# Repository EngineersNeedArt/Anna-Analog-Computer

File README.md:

# “Anna” Analog Computer

***Anna*** is an ecosystem of analog computing modules. The modules (each about the size of a matchbook) make use of a hobbyist breadboard and USB power that combine to make something like an analog computer trainer.

### Breadboard

An electronics breadboard is an integral part of ***Anna***. The breadboard allows ***Anna*** to be easily modular, expandable. It provides a power bus (the top two power rails of the breadboard) and it is acts as the “patch bay” that allows you to connect inputs and outputs between the various analog operators.

### Power

The modules comprising ***Anna*** all run on (nominally 5V) USB power. All modules but **MAIN** assume that the top two power rails of the breadboard supply this USB power. The top rail (row) of the breadboard is assumed to be +5V and the rail (row) below is assumed to be ground (GND).

While these power rails operate the electronics for each module, these rails are not to be used for the analog *programming*. There are instead three reference voltages used in the analog computing domain. These are:
- **+UNIT**, nominally 4.00V. Representing the largest machine value (+1 if you like).
- **ZERO**, nominally 2.50V. Representing the machine value zero (0).
- **-UNIT**, nominally 1.00V. Representing the smallest machine value (-1 if you like).
Needless to say, this makes the voltage window for representing values in ***Anna*** a very narrow 3 volts. Perhaps this is a good time to remind you that it is intended to be a *hobbyist* analog computer. 

## **The Modules**

### MAIN Module

The **MAIN** module is required for any ***Anna*** configuration as it provides USB power to the top two rails of the breadboard. These USB power rails are what all other ***Anna*** modules depend upon to operate.
- Provides USB power to the top two power rails on the breadboard—powering all other ***Anna*** modules.
- Provides the reference voltages for **+UNIT**, **ZERO** and **-UNIT**. These are the operating voltages of the analog computer programs.
- Inputs for up to five source voltages for display on the color LCD.
- Numerous metering modes (can be cycled through using the top button on the module).
- Overload LED (and output pin) indicate when a source voltage is out of range (higher than **+UNIT** or lower than **-UNIT**).

More (esoteric) details are available in the **README** that with the **MAIN** subfolder in this repository.

### POTS Module

The **POTS** module, as with the remaining modules described, is to be inserted into a breadboard such that its power pins engage in the top two power rails (top-most row: **USB 5V**, the row just below: **GND**). As described above, the **USB** power is provided by the **MAIN** board.

The **POTS** has four potentiometers—three of those are wired internally to behave as “coefficient multipliers” (in analog computer parlance). What this means, electrically, is that the low-side of the potentiometer is tied to a *machine zero* reference supplies by **MAIN**, while the user is expected to connect their input signal to the pin tied to the potʼs high-side. With the potʼs wiper connected to the output pin, the pot acts as a voltage divider—effectively attenuating the incoming voltage.

A practical use case for a coefficient multiplier is to attenuate a signal that is being used as feedback.

The 4th potentiometer on the **POTS** module is not tied to a zero-reference—the high-side of the pot is another input pin. The input pins are labeled **CCW** and **CW** referring to the rotation of the pot they correspond to. Connecting **CCW** to a **ZERO** reference makes this 4th pot behave like the other three—like a coefficient multiplier.

Like all of the modules (except for **MAIN**), **POTS** requires a **ZERO** voltage reference for the three coefficient multipliers to work correctly. The modules use op-amps employing a *virtual ground*. As indicated earlier, rather than the analog *voltages* swinging positive and negative to indicate positive and negative *values*, “zero” for ***Anna*** is 2.50V— positive values are from 2.50V to 4.00V, negative values from 2.50V down to 1.00V. So that all the modules are on the same page, they require the virtual ground connected to them from the **MAIN** module (a pin labeled **ZERO**).

(Strictly speaking, if you are using only the fourth potentiometer, you can leave off the **ZERO** reference input.)

All four pots buffer their output (using op-amps as voltage followers).

### ADD Module

The **ADD** module also requires **USB** power and also a **ZERO** reference voltage.

The **ADD** module has a pair of addition operators. (Or *summers*? I don't know: a “summer” is a season and an “adder” is a snake—they're both poor words). These operators take 2 or more inputs (values/voltages) and output the negative sum of those inputs.

#### Overload 

Analog computers programs have to be careful to avoid a condition referred to as **overloading**. The addition operation makes a good case for the problem. Given the voltage limitation of ***Anna*** (1V to 4V, i.e. *machine -1* to *machine +1*) what do we expect if we try to add 4V and 4V (*machine +1* plus *machine +1*)? To dive into the technical, the underlying op-amps that comprise the analog circuitry physically cannot exceed their own power rails—which we have mentioned are **5V USB** and **GND**. So a sum of 8V is already out of the question.

Instead, this condition is considered an error, called **overload**. The "programmer" must re-evaluate the program they have patched together—re-implement it to avoid overload. This might involve artificially scaling down part of an equation and then later "de-scaling" to counter.

There is no on-board overload warning on the **ADD** module. Wiring the output of any add operator to one of the voltage source inputs of **MAIN** though will catch any overloads (**MAIN** detects over/undervolts at all its inputs).

Also, going too negative (below 1V in the case of ***Anna***) is oddly also called an *overload*.

#### Inversion

You may notice that the add operators return the *inverted* sum of the inputs. That is, if you input the values for 0.2 and 0.4, the sum operator will return not 0.6 but -0.6. There is an underlying (op-amp related) reason for this. When the result of adding is needed to act as negative feedback in an equation you are modeling, this inversion is a happy accident. At times though when you need the non-inverted sum, you will have to wire the output of a summer to an inverter operator.

Any add operator with a single input will return that input value inverted as output. But since inverting is a common operation, the **ADD** module contains a pair of dedicated inverter operators. (A dedicated inverter of course needs less pins and so conserves breadboard real-estate).

### MULT Module

The **MULT** module has a pair of multipliers. It performs multiplication using a PWM circuit (described in more detail in the **MULT** ReadMe.md). It requires **USB** power and a **ZERO** reference voltage.

The multiplier and multiplicand are assumed to be within *machine range* and are treated as values between 1.0 and -1.0. As such, the product will also always be within *machine range* (between 1.0 and -1.0). Consequently, the operator should not overload. (If the product ever overloads it is from an input that was already overloaded.)

A test point and two trim pots are there to allow the multiplier to be calibrated. (This requires an oscilloscope in order to adjust a triangle wave to run between 1.00 and 4.00 Volts.) After calibrating a **MULT** module, I measured it with 49 sample voltages (combinations of 7 voltages for **X** and 7 for **Y**) and measured the product. Plotting the results vs. the expected result I submitted the data to an LLM and was told the overall accuracy to be about 2.3% RMS full scale (I am lazy beyond some threshold). In general, expect some error from the **MULT** module.

### INT Module

The **INT** module may be the most important one. I have read that integration was in fact the reason for early analog computing at all.

**INT** combines a pair of integrators in a single module. A single **Reset** button, when held for a short period, sets both integrators to their initial conditions (initial voltages). The “IC” of each integrator is established from the user having connected a voltage to its **IC** pin.

Integrators output a voltage—initially they are expected to be Reset and so output their IC voltage. Inputs to each integrator though can cause the output voltage of the integrator to rise or fall—the applied voltage or value is being integrated with respect to time.

Like the **ADD** module, the integrators on the **INT** module are also inverting. In practice this means that if you supply a **positive** *machine value* to an integrator, the value it outputs will get **smaller**, not larger. The reverse is the case when a **negative** machine value is applied.

If *machine zero* (**ZERO**) is applied as in input, the output of an integrator does not change.

Integrators integrate with respect to time and there is a switch on **INT** that can toggle between a *slow* integration time constant and a *fast* one. In practice, most simulations (programs), might prefer the faster integration—such as a program that models the bounce of a mass on a spring. Another program, like a game simulating a spacecraft landing on the Moon, might want to be slowed down in order to be more easy to play.

## **Future Modules**

There are some “missing modules” that will perhaps show up over time.

### Log and Anti-log Modules

Searching through older analog computer sources, you can find circuits that take a voltage as input and then output the natural **log** of that voltage. A diode (or more typically, a transistor) is employed in the *feedback loop* of an op-amp to achieve this.

Further, a diode (transistor) employed in *series* with the input to an op-amp will give you the **anti-log** from an input voltage.

*(It might be noted that the accuracy of both circuits is (apparently) encumbered by their sensitivity to temperature.)*

If a value is first passed to the **log** circuit, the result can be divided by two with a **coefficient multiplier**—the **anti-log** of this then gives you the square root of the original value.

Or, the **log** of two values can be added with an **adder** and the **anti-log** of the sum is the equivalent of the product of the original values. (Another method of multiplication.)

### Comparator Module

For some simulations a kind of *binary switch* might be desirable. For example, a bouncing ball simulation needs to know when the ball has fallen to some position where it has encountered the floor and should reverse its velocity (it should bounce). A **comparator** module would make use of an op-amp to detect when the input has crossed some threshold and then switch its output.

### Sweep Module

Some simulations might benefit by having an input that sweeps a range of values. A circuit that outputs a triangle wave would achieve this. Having a means to change the speed (period) of the sweep would be important.

### Trigonometry Module

Sine and cosine are useful operations to include. There are no simple electrical circuits that naturally give rise to these trigonometric functions. There is a method using diodes and resistors to *shape* a function from a given input. Enough diode stages in a kind of ladder configuration with precise resistor values can output a voltage that approximate, for example, the sine of the input voltage.

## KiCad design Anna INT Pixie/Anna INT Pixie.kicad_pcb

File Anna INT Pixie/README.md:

# INT Module

The **INT** module consists of a pair of integrators. One of the integrators has three inputs and the other has two.

<div align="center">
  
</div>

## Zero

It will probably come as no surprise that the **INT** module also expects a *machine zero* reference as input. Like the **ADD** module, *machine zero* (ZERO) is used as a *virtual ground* on the non-inverting input of the op-amps.

Like the **ADD** module, this is why the output of the integrator is inverted. Since input values/voltages are connected to the inverting input, they have an inverse effect on the output of the integrator. A positive value (voltage above 2.5V) will in fact cause the integrator output to decrease while a negative value (a voltage below 2.5V) causes the integrator output to become more positive.

## Reset

Each integrator has an *initial condition* (IC) input. This is a value/voltage that the user supplies to be the starting value (output) for each integrator. A single momentary switch, when held down for a short time, resets both integrators to this initial condition.

## Integration Speed

Unlike the other **“Anna”** modules, the integrators have a kind of *speed* associated with them—the speed of integration. The value of the input resistors and the size of the capacitor in the op-amp feedback circuits contribute to determine the speed of integration.

It was found that some simulations, like *Lunar Lander* for example, preferred a slower integration time—to allow the player to react to their descending spacecraft. Other simulations, such as a mass on a spring, felt more realistic with a faster integrator.

To address either scenario, the **INT** module has a separate switch for each integrator that allows for toggling in or out of the op-amp feedback an additional capacitor. With just the one capacitor in the feedback path, an integrator will run faster for simulations like the *spring and mass*. Switching in a second capacitor in parallel slows the integration down by roughly an order of magnitude—making a game like *Lunar Lander* playable.

## Summing Junctions

Like the **ADD** module, the **INT** module also makes accessible the “summing junction” for each integrator. The summing junction is where all the inputs tie together and connect to the inverting input of an op-amp.

If a user wishes for an additional input, a 1 MΩ input resistor can be connected in series with the input and one of the summing junctions on the **INT** module.

Alternatively, if a smaller resistor value is used as an input resistor, such as a 100 kΩ resistor, that input will move the integrator 10x (ten times) as fast. It is possible then to have a much quicker integrator (or much slower) by using input resistors other than 1 MΩ.

## TODO

• Claude suggested adding a "pull to ZERO" resistor on every input. (Perhaps using 10MΩ resistors.)

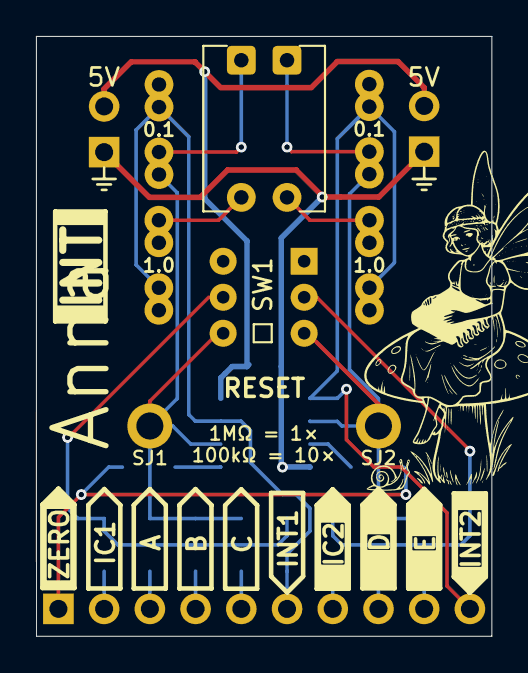
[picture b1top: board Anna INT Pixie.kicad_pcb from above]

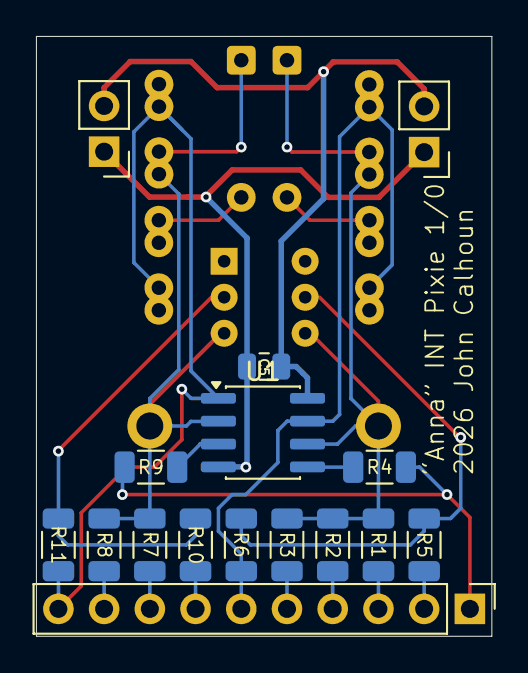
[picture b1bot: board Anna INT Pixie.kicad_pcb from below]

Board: 2 copper layers, 25.3 x 33.3 mm, 25 parts (16 on the bottom side), 19 nets.

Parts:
0.1, 0.1#2: 0.1 µF; C_Rect_L7.0mm_W3.5mm_P2.50mm_P5.00mm
1.0, 1.0#2: 1 µF; C_Rect_L7.0mm_W3.5mm_P2.50mm_P5.00mm
C5: 0.1 µF; C_0805_2012Metric
J1: Conn_01x10_Pin; PinHeader_1x10_P2.54mm_Vertical
J2, J3: Conn_01x02_Pin; PinHeader_1x02_P2.54mm_Vertical
R1, R2, R3, R4, R7, R8, R9: 1 MΩ; R_1206_3216Metric
R5, R6, R10, R11: 100 kΩ; R_1206_3216Metric
SJ1, SJ2: TestPoint; TestPoint_THTPad_2.0x2.0mm_Drill1.0mm
SW1: SW_DPDT_x2; SW_Push_2P2T_Momentary_Anna_INT
SW2, SW3: SW_DIP_x01; SW_DIP_SPSTx01_Piano_10.8x4.1mm_W7.62mm_P2.54mm
U1: MCP6002-xMC; SOIC-8_3.9x4.9mm_P1.27mm

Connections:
+5V: C5.1, J2.2, J3.2, U1.8 (V+)
/A: J1.3, R1.2
/B: J1.4, R2.2
/C: J1.5, R3.2
/E: J1.9, R8.2
/IC1: J1.2, R5.2
/IC2: J1.7, R10.2
/INT1: 0.1.2, 1.0.2, J1.6, R6.1, U1.7
/INT2: 0.1#2.2, 1.0#2.2, J1.10, R11.1, U1.1
/ZERO: J1.1, R4.1, R9.1
GND: C5.2, J2.1, J3.1, U1.4 (V-)
unnamed: 1.0.1, SW2.2
unnamed: 1.0#2.1, SW3.2
unnamed: R10.1, R11.2, SW1.2 (B)
unnamed: 0.1#2.1, R7.1, R8.1, SJ2.1 (1_1), SW1.3 (C), SW3.1, U1.2 (-)
unnamed: R5.1, R6.2, SW1.5 (B)
unnamed: 0.1.1, R1.1, R2.1, R3.1, SJ1.1 (1_1), SW1.6 (C), SW2.1, U1.6 (-)
unnamed: R9.2, U1.3 (+)
unnamed: R4.2, U1.5 (+)

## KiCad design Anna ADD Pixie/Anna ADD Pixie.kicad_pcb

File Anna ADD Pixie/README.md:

# ADD Module

Like the other **“Anna”** modules, the **ADD** module is powered by 5V (nominal) USB voltages. Pins along the top edge are placed and spaced to draw USB power from the top two *power rails* of a standard electronics breadboard. The circuitry of the **ADD** module consists of operational amplifiers (op-amps) to perform the adding of voltages—the USB power limits the output of the **ADD** module to within the 0V to 5V range.

Also like the most of the other **“Anna”** modules, the **ADD** module requires a “zero” reference of 2.50V. An input pin in the lower-left corner of the PCB is provided for this reference voltage to be supplied. The 2.50V is supplied to the non-inverting input of the op-amps that perform the operations and therefore acts as a *virtual ground*.

## Overload

Currently there is no **overload** detection on the **ADD** module itself. If the result of operating on an input voltage results in a voltage outside of the range of **“Anna's”** defined machine range of 1.0V and 4.0V, it is simply presented as is. The **MAIN** module has overload detection on all five of its source voltage inputs and is typically where you will detect an overload.

<div align="center">
  
</div>

## Summing Junction

The schematic (above) shows four op-amps, their non-inverting inputs tied to virtual ground (“zero”, 2.50V). Adder **A** has three inputs and adder **B** has two—these are connected to the inverting inputs of the corresponding op-amps. In both cases, where the inputs tie together (known as the *summing junction*) and test-point is provided such that a user can join additional inputs if desired.

Input resistors on the **ADD** module are 100 kΩ. If similar resistor values are used for additional inputs at the summing junction, the extra inputs will be added normally. However, an input resistor value 10x (ten times) 100 kΩ (1 MΩ) will “weigh” the input by 0.1x (one-tenth). An input resistor that is 0.1x of 100 kΩ (10 kΩ) has the opposite weighting effect—the input is treated as 10x (ten times).

## Inverted Output

By connecting the inputs to be added to the inverting input of the op-amp, the result will also be inverted—the inverted sum of the input voltages. This is why the **ADD** module returns the negative sum (-SUM). I am not expert enough in electronics to understand fully why we use the inverting input for the summing junction.

From an LLM (since this is where it gets fuzzy for me), “The summing junction works because each voltage input behaves independently—seeing only its source voltage across its input resistor, with virtual ground on the other end. That virtual ground exists at the inverting input because the op-ampʼs feedback loop continuously drives it to match the actual ground connected to the non-inverting input. You canʼt simply swap the summing junction to the non-inverting input because virtual ground only exists at the inverting input—without it, the inputs interact with each other and the clean superposition breaks down.”

## Inverters

When analog computing, it turns out that inverting a value is common enough that the **ADD** module dedicates two op-amps just to take an input and return the inverted output. While any **ADD** operator will do the same with a single input, the dedicated inverters save on “breadboard real-estate” (number of pins).

## TODO

• Claude suggested adding a "pull to ZERO" resistor on every input. (1MΩ to 10MΩ)

• S.J. (summing junction) hole is the wrong size.

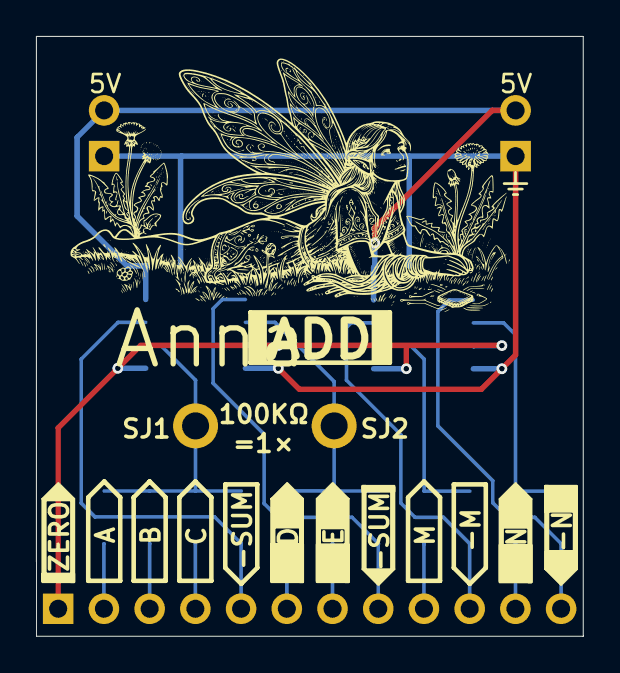
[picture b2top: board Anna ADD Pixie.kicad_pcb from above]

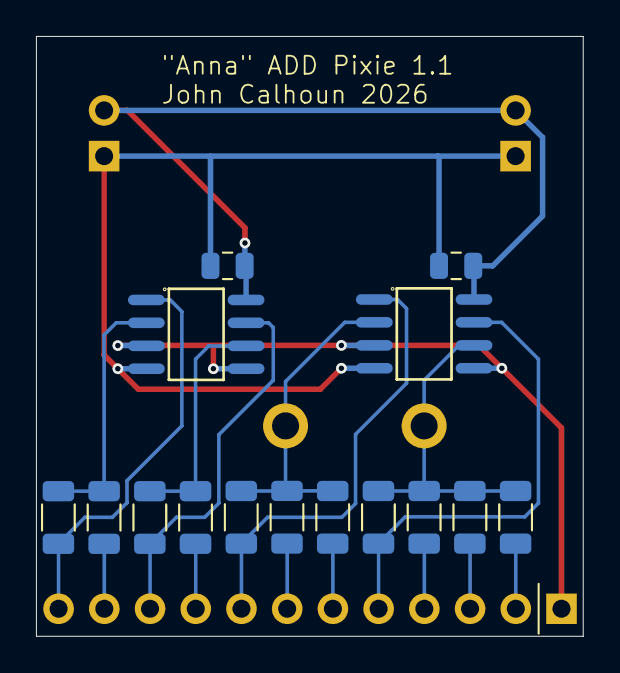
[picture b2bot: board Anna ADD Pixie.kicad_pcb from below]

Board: 2 copper layers, 30.4 x 33.3 mm, 20 parts (18 on the bottom side), 18 nets.

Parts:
C4, C5: 0.1 µF; C_0805_2012Metric
J1: Conn_01x13_Pin; PinHeader_1x12_P2.54mm_Vertical
J2, J3: Conn_01x02_Pin; PinHeader_1x02_P2.54mm_Vertical
J4, J5: Conn_01x01_Socket; PinSocket_1x01_P2.54mm_Vertical
R1, R2, R3, R4, R5, R6, R8, R9, R10, R11, R12: 100 kΩ; R_1206_3216Metric
U1, U2: MCP6002-xMC; SOIC-8_L4.9-W3.9-P1.27-LS6.0-BL

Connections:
GND: C4.2, C5.2, J2.1, J3.1, U1.4 (V-), U2.4 (V-)
unnamed: J1.1, U1.3 (+), U1.5 (+), U2.3 (+), U2.5 (+)
unnamed: J1.2, R1.2
unnamed: J1.3, R2.2
unnamed: J1.4, R3.2
unnamed: J1.5, R4.2, U2.7
unnamed: J1.6, R5.2
unnamed: J1.7, R6.2
unnamed: J1.8, R8.2, U2.1
unnamed: J1.9, R9.2
unnamed: J1.10, R10.1, U1.7
unnamed: J1.11, R11.2
unnamed: J1.12, R12.1, U1.1
unnamed: C4.1, C5.1, J2.2, J3.2, U1.8 (V+), U2.8 (V+)
unnamed: J4.1, R1.1, R2.1, R3.1, R4.1, U2.6 (-)
unnamed: J5.1, R5.1, R6.1, R8.1, U2.2 (-)
unnamed: R11.1, R12.2, U1.2 (-)
unnamed: R9.1, R10.2, U1.6 (-)

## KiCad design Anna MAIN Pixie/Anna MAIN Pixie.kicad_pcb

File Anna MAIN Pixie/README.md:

# MAIN Module

## Software

**MAIN** features a *daughter board* consisting of an ESP32 Dev Board that includes an LCD display and two soldered-on pushbuttons. Software written for **MAIN** makes use of the display and buttons.

## Metering Modes

The bottom-right button, the one closest to the user, Iʼll call the *mode button*, was chosen to cycle through **MAIN**s various metering modes. The other button, Iʼll call the *options button*, often cycles through various options for the selected metering mode.

### Vertical Meters

<div align="center">

</div>

The default metering mode consists of five moveable, vertical meters and a fixed red index line. They are labeled 1 through 5 and correspond to the inputs on **MAIN**, **SRC1** through **SRC5**. The *options button* allows you to toggle the number of inputs displayed from the 5 down to just 1. Overload is represented by the labels flashing.

### Sweep Meters

<div align="center">

</div>

Looking like traditional analog panel meters, the magic of digital emulation means that 5 needles can share the same meter. They are labeled 1 through 5, color coded, and correspond to the inputs on **MAIN**, **SRC1** through **SRC5**. The *options button* allows you to toggle the number of inputs displayed from the 5 down to just 1. Overload is represented by the labels flashing.

***(NOTE: in the screenshot only 3 inputs are enabled.)***

### Strip Chart

<div align="center">

</div>

The Strip Chart is a moving metering mode that can display all 5 source inputs with roughly 4 seconds of history visible. The vertical rules that scroll by mark off 1 second intervals. The *options button*  allows you to toggle the number of inputs displayed. *Overload* is represented by the labels flashing.

***(NOTE: in the screenshot only 2 inputs are enabled.)***

### XY Scope

<div align="center">

</div>

The XY Scope is patterned after an oscilloscope. It makes use of **SRC1** to control the X-position of a dot and **SRC2** to control the Y-position. The *options button* toggles between displaying the whole *machine value* range to displaying just Quadrant I (the positive *machine values*). The *options button* also toggles between two *fade speeds* for the phosphor trace: slow and fast.

### Spring + Mass

<div align="center">

</div>

Spring + Mass is a special demonstration metering mode. It represents a mass on a spring. The vertical position of the mass is controlled solely by the voltage at **SRC1**. The *options button* does nothing.

The mass leaves a “trail” sort of like the Strip Chart. A color change indicates 1-second intervals.

### Lunar Lander

<div align="center">

</div>

Lunar Lander is another special metering mode that is a game. It expects a gravitational constant to be presented at **SRC1**, the intermittent thrust to be connected to **SRC2**, the spacecraft velocity to be connected to **SRC3** and the spacecraft elevation/altitude to be connected to **SRC4**. An optional *fuel level* voltage can be connected to **SRC5**.

The above connections presume that the user has wired up the lunar lander program on the analog computer—supplied the above voltages as described.

Starting the game is done by simply resetting the integrators that dictate velocity (reset to **ZERO**), altitude (reset to **+UNIT**) and, if the fuel level integrator is wired up, resetting the fuel level to **+UNIT**. Doing so put the spacecraft at the top of the display, with no vertical velocity, and optionally with a full tank of fuel.

As the spacecraft descends, the software monitors the spacecraft altitude (**SRC4**) to determine touch-down. When the spacecraft altitude passes the touch-down threshold, velocity (**SRC3**) is evaluated by the software to determine if the landing was safe. The **MAIN** display will indicate a safe landing or a crash.

If the optional fuel level (**SRC5**) ever drops to an empty tank, the game will indicate a crash landing.

### Raw Values

<div align="center">

</div>

Initially kind of a debug mode, it displays the raw values of the inputs coming off the ADCs (Analog to Digital chips). In addition to **SRC1** through **SRC5** though, it also shows the measured values for **+UNIT**, **ZERO** and **-UNIT**.

When a source input is indicated as Overloading, it is because it is outside the range of the measured **+UNIT** and **-UNIT**. It is indicated in this mode when the inputʼs label is rendered white. **+UNIT**, **ZERO** and **-UNIT**, by definition, can never be “overloading”.

When a source input is displayed on the LCD, as a reading on a meter for example, it is arrived at by finding where the source input value is proportionally between the reference values (voltages). If, for example, the value is greater than **ZERO**, itʼs relative value is determined by scaling it proportionally between the measured **ZERO** and **+UNIT**.

## Hardware

<div align="center">

</div>

The ESP32 dev board (LILYGO T-Display) dominates the schematic with the large yellow box in the upper right. It has the USB-C connection from which the entire **“Anna”** ecosystem derives USB power. A pair of capacitors serve to smooth the current on those power rails.

### Buffering

Across the bottom are eight op-amps involved in buffering (wired as voltage followers). Three are used to buffer the outputs of the machine values/voltages (1.0V, 2.5V and 4.0V)—in this way the voltages are protected from being loaded down by the analog circuitry.

The other five op-amps are used to buffer the five source-voltage inputs to **MAIN**. 

### ADC

Just above the op-amps are a pair of ADC chips (analog-to-digital). Each chip has four channels for a total of eight inputs. Three of these are dedicated to converting the machine values/voltages (1.0V, 2.5V and 4.0V) to digital form. The other five are, unsurprisingly, used to convert the source-voltage inputs (**SRC1** through **SRC5**) to digital form.

The ESP32 reads the 8 digital values over I2C.

*Note: the ESP32 works on 3.3V and can be damaged by the 5V that **“Anna”** uses. The ADC chips are running from 5V and can therefore directly interface **“Anna's”** 5V inputs. To interface between the ADC chips and the ESP32, a dedicated chip handles level-shifting the I2C connection.*

When, for example, the ESP32 is to display a source-voltage input as a needle on a meter, it can use the three digital machine values to find a proportional position to move the needle to.

Further, if any digital source-voltage input exceeds the digital positive machine unit value or is less than the digital negative machine unit value, it is flagged as **overloading**.

### Voltage Sources

A last point to call out is the small component on the far-left (U5). It takes the voltage from USB and provides the stable 4.0V that **“Anna”** uses for positive machine value. The other machine values (zero and negative unit), are pared from the 4.0V using carefully selected resistor values arranged as voltage dividers.

## TODO

• The holes that receive the ESP32 Dev Board on the PCB are still a little tight. Open them up to the next drill size.

• I'm not a fan of the super-tiny SMD resistors. Perhaps move up to the next SMD resistor size.

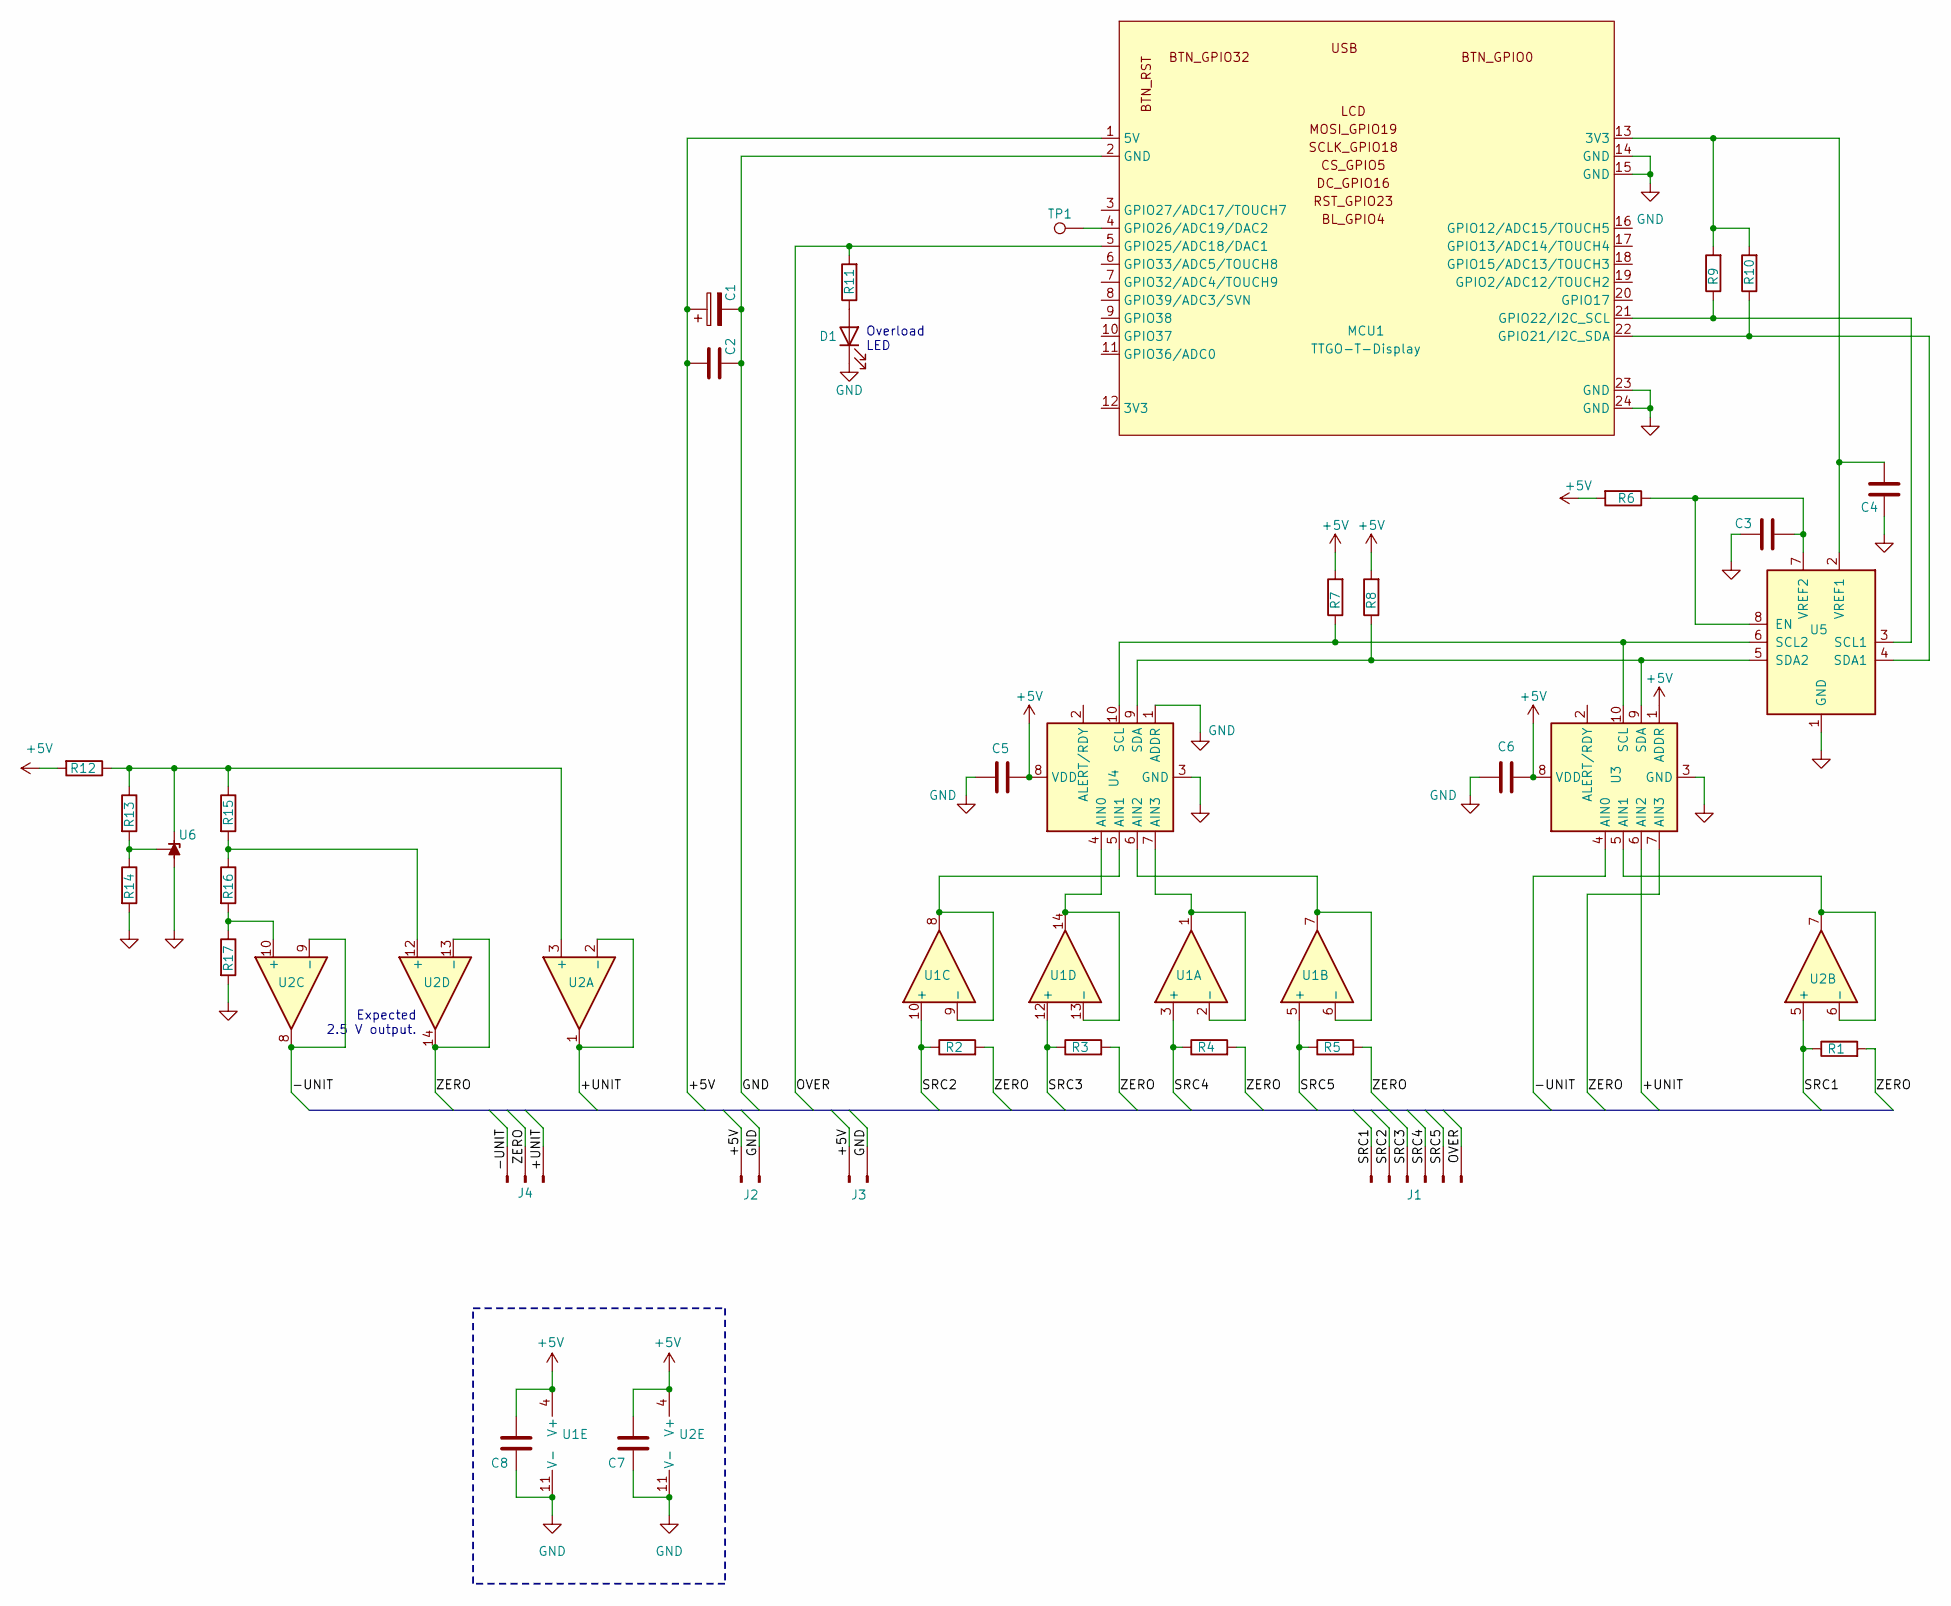
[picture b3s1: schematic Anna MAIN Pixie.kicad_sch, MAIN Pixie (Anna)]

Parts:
C1: 100 µF; CP_Elec_6.3x5.4; LCSC C97805
C2, C3, C4, C5, C6, C7, C8: 0.1 µF; C_0805_2012Metric; LCSC C49678
D1: LED; LED_1206_3216Metric; LCSC C49018
J1: Conn_01x06_Pin; PinHeader_1x06_P2.54mm_Vertical
J2, J3: Conn_01x02_Pin; PinHeader_1x02_P2.54mm_Vertical
J4: Conn_01x03_Pin; PinHeader_1x03_P2.54mm_Vertical
MCU1: TTGO-T-Display
R1, R2, R3, R4, R5: 100 kΩ; R_0603_1608Metric; LCSC C25803
R6: 330 kΩ; R_0603_1608Metric; LCSC C23137
R7, R8, R9, R10: 4.7 kΩ; R_0603_1608Metric; LCSC C23162
R11: 680 Ω; R_0805_2012Metric; LCSC C17798
R12: 47 Ω; R_0603_1608Metric; LCSC C114623
R13: 6.04 kΩ (0.1%); R_0603_1608Metric; LCSC C728595
R14, R17: 10 kΩ (0.1%); R_0603_1608Metric; LCSC C95204
R15, R16: 15 kΩ (0.1%); R_0603_1608Metric; LCSC C326733
TP1: TestPoint; TestPoint_THTPad_1.5x1.5mm_Drill0.7mm
U1, U2: MCP6004; SOIC-14_L8.7-W3.9-P1.27-LS6.0-BL; LCSC C7378
U3, U4: ADS1015; VSSOP-10_3x3mm_P0.5mm; LCSC C701605
U5: PCA9306DCUT; VSSOP-8_2.3x2mm_P0.5mm; LCSC C33196
U6: TL431DBZ; SOT-23-3; LCSC C350683

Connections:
+5V: C1.1, C2.1, C5.2, C6.2, C7.2, C8.2, J2.1, J3.1, MCU1.1 (5V), R6.2, R7.2, R8.2, R12.2, U1.4 (V+), U2.4 (V+), U3.1 (ADDR), U3.8 (VDD), U4.8 (VDD)
/+UNIT: J4.3, U2.1, U2.2 (-), U3.6 (AIN2)
/-UNIT: J4.1, U2.8, U2.9 (-), U3.4 (AIN0)
/OVER: J1.6, MCU1.5 (GPIO25/ADC18/DAC1), R11.2
/SRC1: J1.1, R1.1, U2.5 (+)
/SRC2: J1.2, R2.1, U1.10 (+)
/SRC3: J1.3, R3.1, U1.12 (+)
/SRC4: J1.4, R4.1, U1.3 (+)
/SRC5: J1.5, R5.1, U1.5 (+)
/ZERO: J4.2, R1.2, R2.2, R3.2, R4.2, R5.2, U2.13 (-), U2.14, U3.7 (AIN3)
GND: C1.2, C2.2, C3.1, C4.1, C5.1, C6.1, C7.1, C8.1, D1.1 (K), J2.2, J3.2, MCU1.2 (GND), MCU1.14 (GND), MCU1.15 (GND), MCU1.23 (GND), MCU1.24 (GND), R14.2, R17.2, U1.11 (V-), U2.11 (V-), U3.3 (GND), U4.1 (ADDR), U4.3 (GND), U5.1 (GND), U6.3 (A)
unnamed: D1.2 (A), R11.1
unnamed: MCU1.22 (GPIO21/I2C_SDA), R10.1, U5.4 (SDA1)
unnamed: MCU1.21 (GPIO22/I2C_SCL), R9.1, U5.3 (SCL1)
unnamed: MCU1.4 (GPIO26/ADC19/DAC2), TP1.1
unnamed: U1.1, U1.2 (-), U4.7 (AIN3)
unnamed: U1.6 (-), U1.7, U4.6 (AIN2)
unnamed: U1.8, U1.9 (-), U4.5 (AIN1)
unnamed: U1.13 (-), U1.14, U4.4 (AIN0)
unnamed: R12.1, R13.1, R15.1, U2.3 (+), U6.1 (K)
unnamed: U2.6 (-), U2.7, U3.5 (AIN1)
unnamed: R16.2, R17.1, U2.10 (+)
unnamed: R15.2, R16.1, U2.12 (+)
unnamed: R7.1, U3.10 (SCL), U4.10 (SCL), U5.6 (SCL2)
unnamed: R8.1, U3.9 (SDA), U4.9 (SDA), U5.5 (SDA2)
unnamed: C3.2, R6.1, U5.7 (VREF2), U5.8 (EN)
unnamed: C4.2, MCU1.13 (3V3), R9.2, R10.2, U5.2 (VREF1)
unnamed: R13.2, R14.1, U6.2 (REF)

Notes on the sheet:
Expected 2.5 V output.
Overload LED

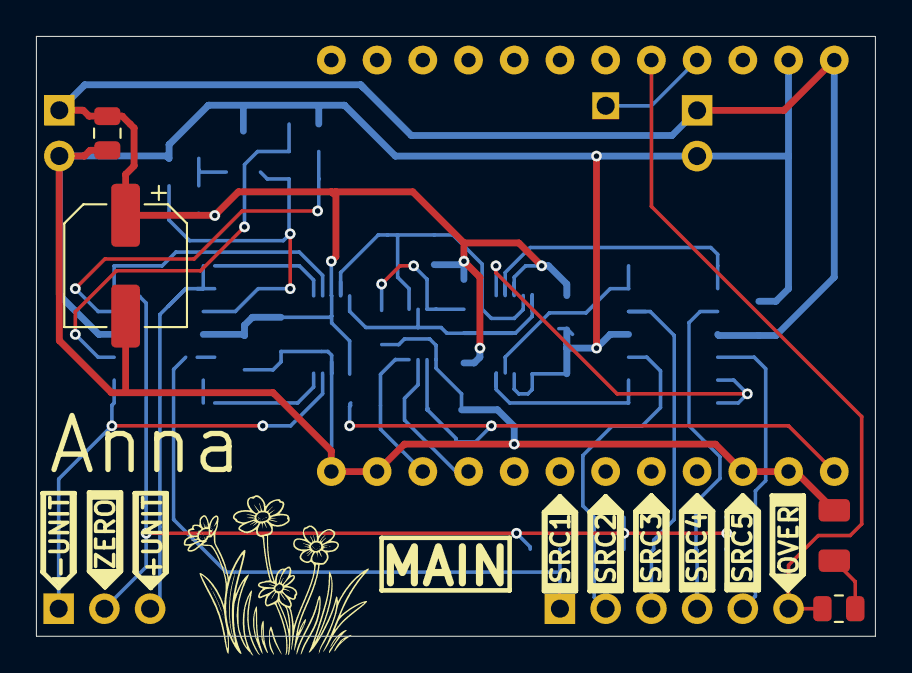
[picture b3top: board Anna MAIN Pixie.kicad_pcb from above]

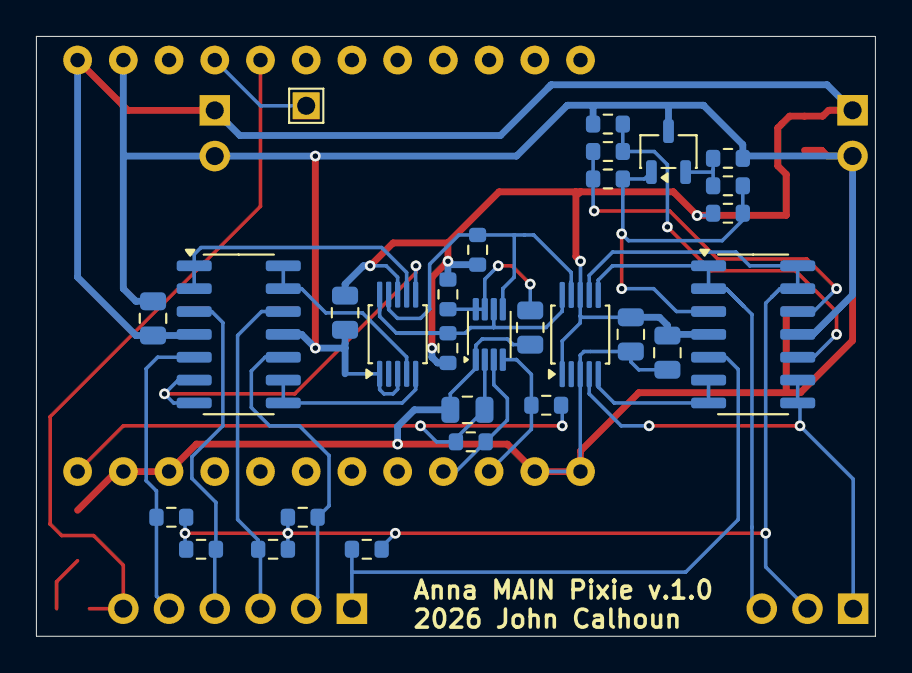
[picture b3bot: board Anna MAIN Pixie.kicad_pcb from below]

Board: 2 copper layers, 46.6 x 33.3 mm, 38 parts (33 on the bottom side), 28 nets.

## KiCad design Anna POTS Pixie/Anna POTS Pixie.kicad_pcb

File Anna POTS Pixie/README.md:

# POTS Module

Four op-amps buffer the outputs from the four potentiometers of the **POTS** module. In this way, circuits connected to the output to not load the potentiometer and drag down itʼs voltage.

<div align="center">
  
</div>

## Coefficient Multipliers

Again, as with the other modules (excluding **MAIN**), we have a **ZERO** input that is expected to be the *Zero* machine value (2.5V provided by **MAIN**). In the case of **POTS** though it is used merely as the CCW (counter-clockwise) input on each of three potentiometers. In this way, the potentiometers behave as (to use analog computing terminology) *coefficient multipliers*. That is, given an input value/voltage on the other end of the pot, the wiper of the pot will present (output) a value/voltage between input and *machine zero*. In this way it is *attenuating* the input (multiplying by a factor between 0.0 and 1.0).

A common use-case for a coefficient multiplier in analog computing might be to feedback some portion of a value, perhaps from an integrator, back into itʼs input. For example, if an integrator is representing velocity, a portion of that velocity might be used to represent the friction impeding the velocity. A coefficient multiplier allows you to dial in a coefficient of friction.

Another common use case is to present a value/voltage less than the *positive machine unit* or greater than the *negative machine unit*.

## Open-Ended Potentiometer

The fourth potentiometer is not tied to *machine zero*—both ends of the potentiometer are user inputs. This is more open-ended potentiometer—allowing the user to connect any value/voltage pair to the inputs and use the pot knob to select an output value/voltage anywhere in between. If *positive machine unit* is connected as one input and *negative machine unit* connected to the other, the output (wiper) can represent all machine values for **“Anna”**.

Further, if you should connect *machine zero* to the CCW (counter-clockwise) input, you have a fourth coefficient multiplier.

## Power

Not shown in the schematic, the op-amps, again, are powered from the (nominal) 5V USB power in the same way the rest of **“Annaʼs”** modules are.

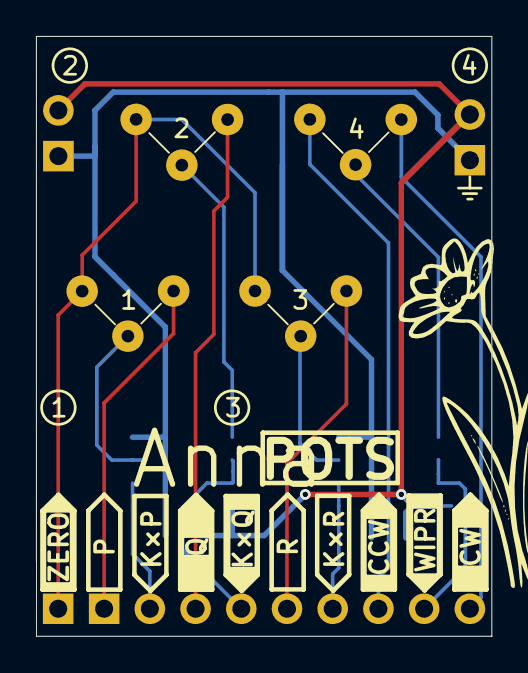
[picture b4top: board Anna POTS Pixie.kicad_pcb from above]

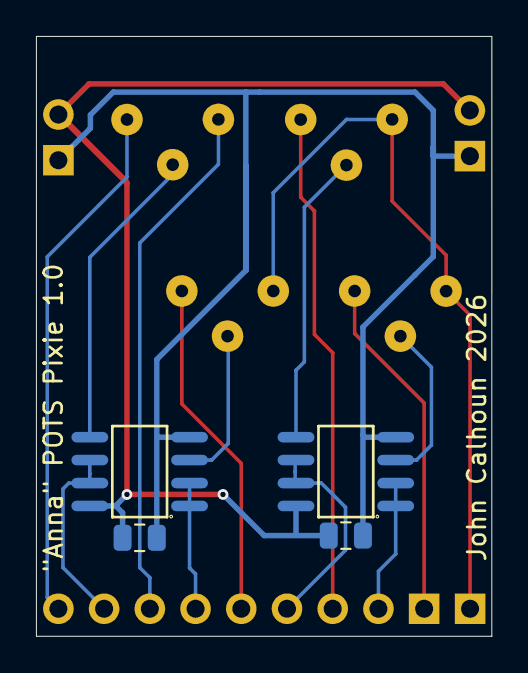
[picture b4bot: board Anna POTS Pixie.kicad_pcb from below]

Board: 2 copper layers, 25.3 x 33.3 mm, 12 parts (8 on the bottom side), 16 nets.

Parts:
1, 2, 3, 4: R_Potentiometer; Potentiometer_Blue_Trimpot_Universal
C1, C2: 0.1 µF; C_0805_2012Metric
J1: Conn_01x01_Pin; PinHeader_1x01_P2.54mm_Vertical
J2, J3: Conn_01x02_Pin; PinHeader_1x02_P2.54mm_Vertical
J4: Conn_01x09_Pin; PinHeader_1x09_P2.54mm_Vertical
U1, U2: MCP6002-xMC; SOIC-8_L4.9-W3.9-P1.27-LS6.0-BL

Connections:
GND: C1.2, C2.2, J2.1, J3.1, U1.4 (V-), U2.4 (V-)
unnamed: 1.1, 2.1, 3.1, J1.1
unnamed: C1.1, C2.1, J2.2, J3.2, U1.8 (V+), U2.8 (V+)
unnamed: 1.3, J4.1
unnamed: J4.2, U2.1, U2.2 (-)
unnamed: 2.3, J4.3
unnamed: J4.4, U2.6 (-), U2.7
unnamed: 3.3, J4.5
unnamed: J4.6, U1.1, U1.2 (-)
unnamed: 4.1, J4.7
unnamed: J4.8, U1.6 (-), U1.7
unnamed: 4.3, J4.9
unnamed: 3.2, U1.3 (+)
unnamed: 4.2, U1.5 (+)
unnamed: 1.2, U2.3 (+)
unnamed: 2.2, U2.5 (+)

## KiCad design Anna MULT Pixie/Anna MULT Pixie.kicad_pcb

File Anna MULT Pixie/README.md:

# MULT Module

The **MULT** module has two multiplier operators. Both take a pair of values assumed to be within *machine range* (between 1.0V and 4.0V). Each outputs the product of the two inputs. The outputs (products) from the **MULT** module are not inverted as they are for the **INT** and **ADD** module. This is because the **MULT** module works very differently (as is discussed below).

### ZERO

Before going further though, like the other operator modules, *machine zero* (**ZERO**, 2.5V) is a required input. The usual way to do this is to connect a wire from the **MAIN** module's **ZERO** voltage output.

### Multiplication Operation

As stated, the two values to be multiplied are assumed to be between *-UNIT* and *+UNIT*. The multiplier operators treat this range of input values as though they represent -1.0 to +1.0. With -1.0 (*-UNIT*) being the smallest value and +1.0 (*+UNIT*) the largest value to be multiplied, it should be clear that, mathematically, the product too will always be within this range. For this reason, the **MULT** module should not ever be a source of *overflow*. (The product should only overflow if one of the multiplicands was already overflowing.)

### Circuit Operation

As stated, multiplication is done in a way very different from the op-amp based modules. Describing how it works is simplified if it is broken down in steps.

<div align="center">
  
</div>

### Triangle Wave

Top-most in the schematic (above) is a circuit that outputs a triangle wave. It consists of a pair of op-amps: the first one acting as an oscillator to create an intermediary square wave, the second op-amp is wired as an integrator such that the incoming square wave causes the final triangular output.

Two trim pots are incorporated in order to adjust the triangle wave such that it peaks at 4.0V (*+UNIT*) and at it's lowest, base voltage, it is at 1.0V (-UNIT).

The purpose of the triangle wave (that oscillates at a frequency of about 4 kHz, FWIW) will be clear below.

### Comparators

Just below the triangle wave circuit (see schematic above again) is one of the multiplicand inputs labeled **X1**. It is connected to the non-inverting input of an op-amp (*U1B*). The inverting input of that op-amp if the triangle wave we described. With op-amp configured as a comparator, the output is going to be high when the non-inverting input is a greater voltage than the inverting input. For our purposes, it means that the op-amp output is high when the multiplicand (*X1*) is greater than the value of the triangle wave.

Let's stop and think about what that means. If **X1** is *machine zero* (recall, 2.5V) and the triangle wave is ramping up and down symmetrically between 1.0V (*-UNIT*) and 4.0V (*+UNIT*), then it should be the case that the output from the comparator is split 50/50 between being high and being low.

If instead **X1** is greater than *machine zero* (greater than 2.5V) then the output from **U1B** should be higher more than 50% of the time. If this sounds to you like **X1** is controlling the *duty cycle* of comparator **U1B**, pat yourself on the back.

You should note that an identical circuit to the one just described exists below on the schematic—for **X1** and **U2B**. I will only be describing the one circuit.

### Switching

Following the schematic, the pulse-width modulated (PWM) output from **U1B** goes to the rather large rectangular circuit/chip. This integrated circuit is an analog switch, and **U1B** is connected to drive one of the internal switches (*S1*). This is the "A" switch in the IC and it controls whether **A0** or **A1** are selected for output **A**.

Recall that if **X1** is *machine zero* we expect a 50% duty-cycle. This would mean that **A** would output **A0** half of the time and **A1** the other half of the time. And what then are **A0** and **A1**?

**A1** is simple, it comes directly from **Y1**, our multiplier.

**A0** is a little more complicated, it comes from an op-amp (*U2A*) acting as an inverting op-amp. In fact, **A0** is **Y1** inverted (the negative value). So if **Y1** is *+UNIT*, **U2A** will output *-UNIT*. Another example, if **Y1** is *machine zero*, the inverted value is also *machine zero*.

What does this mean if we are switching between **Y1** and inverted **Y1**? Before we answer that question, let's look at the final stage of the circuit.

### Filtering

The final stage for our multiplier operator that began with is **X1** and **Y1** is the op-amp (*U1C*) that outputs the product (**X1×1**). This final op-amp is configured as an active filter. It *smooths* the output of switch **A** to a voltage (value) that is the kind of average of the output.

Back to our early example, if we are switching between **Y1** and **-Y1** (inverted **Y1**) and spending 50% of the time at each voltage, the *average* value will be *machine zero*. Does that make sense? If **Y1** is *+UNIT* then **-Y1** will be *-UNIT* and, when averaged, will give *machine zero*.

In fact, this is what we expect mathematically: recall that 50% duty cycle was for an **X1** that was *machine zero*—and any number multiplied by zero if of course zero.

So what happens when **X1** is greater than *machine zero*? We said above that the output of our comparator would be high more often than low in that case. This will correspond to **Y1** being switched in more often than the inverted **-Y1**. And this will *average* out to a value closer to **Y1**.

In the extreme case, if **X1** is *+UNIT* (the largest value and treated as though it is numerically 1.0) then the output of the comparator should remain high and the switched output then simply **Y1**. Again, this is expected as 1.0 times any number is that number.

I'll leave it as an exercise for you to understand the operation of the circuit when **X1** is *-UNIT* or when **Y1** is *machine zero*.

## TODO

• An inverted output would be nice: **-X × Y**. This would require additional op-amps.

• There is a cap that is a touch too close to the edge of the PCB.

• Silkscreen show **X × Y** instead of **XY**. (Perhaps **X ⋅ Y**)

• Larger butterfly art.

• Possibly replace trim pots with specific resistor values found to be correct.

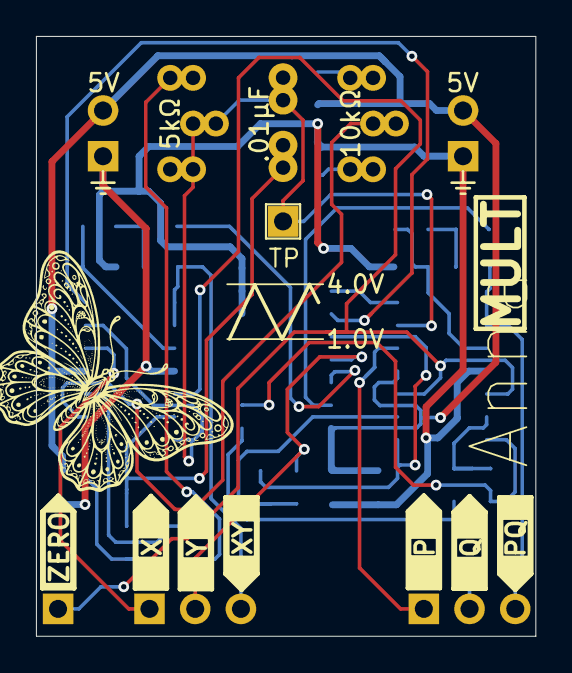
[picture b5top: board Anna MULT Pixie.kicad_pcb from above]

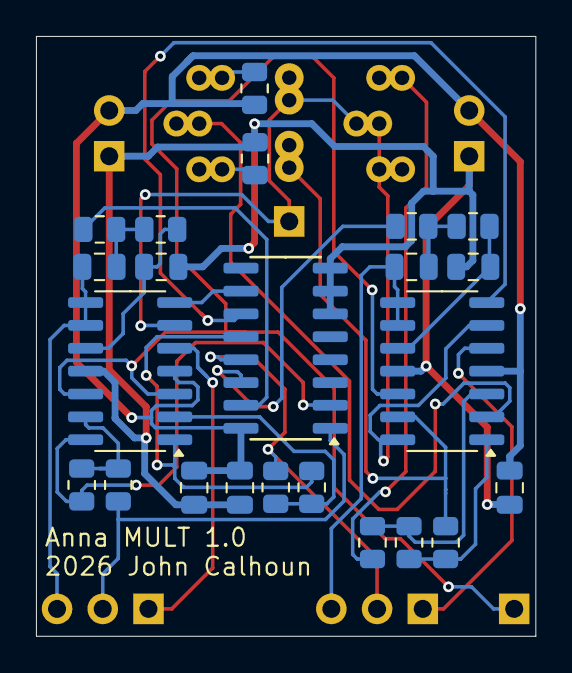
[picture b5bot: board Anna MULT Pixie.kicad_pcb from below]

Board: 2 copper layers, 27.7 x 33.3 mm, 32 parts (28 on the bottom side), 29 nets.

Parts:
5kΩ: 5 kΩ; Potentiometer_Bourns_3296W_Vertical
10kΩ: 10 kΩ; Potentiometer_Bourns_3296W_Vertical
.01µF: 0.01 µF; C_Rect_L7.0mm_W3.5mm_P2.50mm_P5.00mm
C2, C7: 0.033 µF; C_0805_2012Metric
C3, C4, C8: 0.1 µF; C_0805_2012Metric
C5, C6: 0.015 µF; C_0805_2012Metric
J1, J5: Conn_01x03_Pin; PinHeader_1x03_P2.54mm_Vertical
J2, J3: Conn_01x02_Pin; PinHeader_1x02_P2.54mm_Vertical
J4: Conn_01x01_Pin; PinHeader_1x01_P2.54mm_Vertical
R1, R3, R4, R5, R6, R7, R8, R9, R10, R11, R12, R13: 10 kΩ; R_0805_2012Metric
R2: 2.2 kΩ; R_0805_2012Metric
TP: TestPoint; TestPoint_THTPad_1.5x1.5mm_Drill0.7mm
U1, U2: MCP6004; SOIC-14_L8.7-W3.9-P1.27-LS6.0-BL
U3: CD4053B; SOIC-16_3.9x9.9mm_P1.27mm

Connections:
+5V: C3.2, C4.1, C8.1, J2.2, J3.2, R12.2, U1.4 (V+), U2.4 (V+), U3.16 (VDD)
/-Y1: R5.2, U2.1, U3.12 (A0)
/-Y2: R9.2, U2.14, U3.2 (B0)
GND: C3.1, C4.2, C5.2, C6.2, C8.2, J2.1, J3.1, R13.1, U1.11 (V-), U2.11 (V-), U3.6 (INH), U3.7 (VEE), U3.8 (VSS)
unnamed: C2.2, R6.1, R7.2
unnamed: C7.2, R10.2, R11.1
unnamed: R1.2, R3.1, U1.1
unnamed: 5kΩ.1, R2.2
unnamed: 10kΩ.1, R12.1
unnamed: 10kΩ.3, R13.2
unnamed: R1.1, R2.1, U1.3 (+)
unnamed: 10kΩ.2, U1.2 (-)
unnamed: 5kΩ.2, 5kΩ.3, .01µF.2, TP.1, U1.6 (-), U1.14, U2.6 (-)
unnamed: C6.1, R6.2, U1.10 (+)
unnamed: .01µF.1, R3.2, U1.13 (-)
unnamed: R4.2, R5.1, U2.2 (-)
unnamed: C5.1, R11.2, U2.10 (+)
unnamed: R8.2, R9.1, U2.13 (-)
unnamed: R7.1, U3.14 (A)
unnamed: R10.1, U3.15 (B)
unnamed: U1.7, U3.11 (S1)
unnamed: U2.7, U3.10 (S2)
X1: J1.1, U1.5 (+)
X1xY1: C2.1, J1.3, U1.8, U1.9 (-)
X2: J5.1, U2.5 (+)
X2xY2: C7.1, J5.3, U2.8, U2.9 (-)
Y1: J1.2, R4.1, U3.13 (A1)
Y2: J5.2, R8.1, U3.1 (B1)
ZERO: J4.1, U1.12 (+), U2.3 (+), U2.12 (+)

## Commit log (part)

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2026-04-28 Add initial release of the Anna MULT Pixie.
2026-04-28 Added the first release of the ADD Pixie (PCB).
2026-04-29 Pulling in the Arduino sources for the MAIN module.
2026-04-29 Adding ADD and MAIN modules (PCBs, schamtics).
2026-04-29 Experimenting with varying dot size between two modes of oscilloscope. Also two modes now are long and short fade (SLOW and FAST). Seems to be a nice touch.
2026-05-05 Scope mode has a 'quadrant mode' where it displays only Quadrant I. Also, an overlay indicating which metering mode you are in is handled.
2026-05-19 Added a screenshot function for documentation purposes.
2026-05-20 Turned off screendump.
2026-05-20 Begin to add artwork.
2026-05-21 Stub in README.
2026-05-21 Renamed.
2026-05-24 Added two more images.
2026-06-07 Added INT module. Also updated ADD module with larger SJ holes.
2026-06-08 Added images.
2026-06-08 Add README.
2026-06-08 Image directory.
2026-06-08 Add schematic.
2026-06-08 Added schematics and READMEs.
2026-06-23 Alpha better matches actual, physical panel meter.
